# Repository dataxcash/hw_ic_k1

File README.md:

# hw_ic_k1 — K1 Master Gate Card (PCIe 2.1 x2 Injection)

*K1 Master Gate Card — final 4K top render (ECN-14/15/16 complete). USB Type-C
re-mounted facing the board's left edge; all 15 high-speed nets re-routed and
length-matched (intra-pair skew ≤ 0.10 mm); H5 mounting hole added — 47
components, 5 mounting holes. J1 body uses the Amphenol stand-in STEP; the JAE
DX07S024WJ1R350 model is pending.*

Open-source hardware — KiCad design files for the **K1 Master Gate Card**,
the master-side converter card in the IOCONVERT V2.0 1-Master-to-4-Worker
chained NTB cluster.

## Overview

K1 sits at the **master side** of a PCIe NTB chain. It provides USB Type-C
management access, pre-authentication gating (SE050 via I2C), and a PCIe
2.1 x2 data path injected into the master host through an OCuLink connector.

```
KEY (secure vault) ──Type-C──► K1 Master Gate Card ──OCuLink──► Master Host
                                  │
                                  ├─ USB management (SBU I2C ↔ SE050 pre-auth)
                                  ├─ PCIe 2.1 x2 lane injection
                                  └─ 5V pre-auth power rail (TLV61046 boost)
```

## Key Features

- **Form factor**: 80 × 38 mm, 4-layer PCB
- **Interface**: USB Type-C (KEY), OCuLink SFF-8612 (host), 12V DC-in
- **Security**: STM32G0B1 MCU gatekeeper + SE050 pre-authentication via SBU I2C
- **Data path**: PCIe 2.1 x2 with PI3DBS16412 lane-swap MUX
- **Power**: 3.3V_AUX → 5V boost (TLV61046), LDO 5V→3V3, 12V→3V3 DC-DC
- **Management**: OOB UART passthrough, opto-isolated power button (LTV-356T)

## Repository Contents

| Path | Description |
|---|---|
| `k1_v1.kicad_pro` / `.kicad_pcb` | KiCad 10 project + PCB (self-contained) |
| `sch/` | Schematics: connectors, MCU & sideband, power (12V/5V/3V3), decoupling |
| `lib/IOCONVERT.kicad_sym` | Symbol library (80 symbols) — required for schematics |
| `lib/ForgeOS.pretty/` | Footprint library (19 footprints) |
| `boards/` | Board/nets configuration (YAML) |

## Getting Started

1. Install [KiCad](https://www.kicad.org/) 10.x
2. Clone this repository
3. Open `k1_v1.kicad_pro`
4. If symbols/footprints show as missing, add `lib/IOCONVERT.kicad_sym`
   to the symbol library table and `lib/ForgeOS.pretty/` to the footprint
   library table (global or project-level)

## License

AGPL-3.0 (see `LICENSE`)

---

*Part of the IOCONVERT V2.0 family: [hw_ic_k2](https://github.com/dataxcash/hw_ic_k2) (worker data-plane card) · [hw_ic_key](https://github.com/dataxcash/hw_ic_key) (secure key vault)*

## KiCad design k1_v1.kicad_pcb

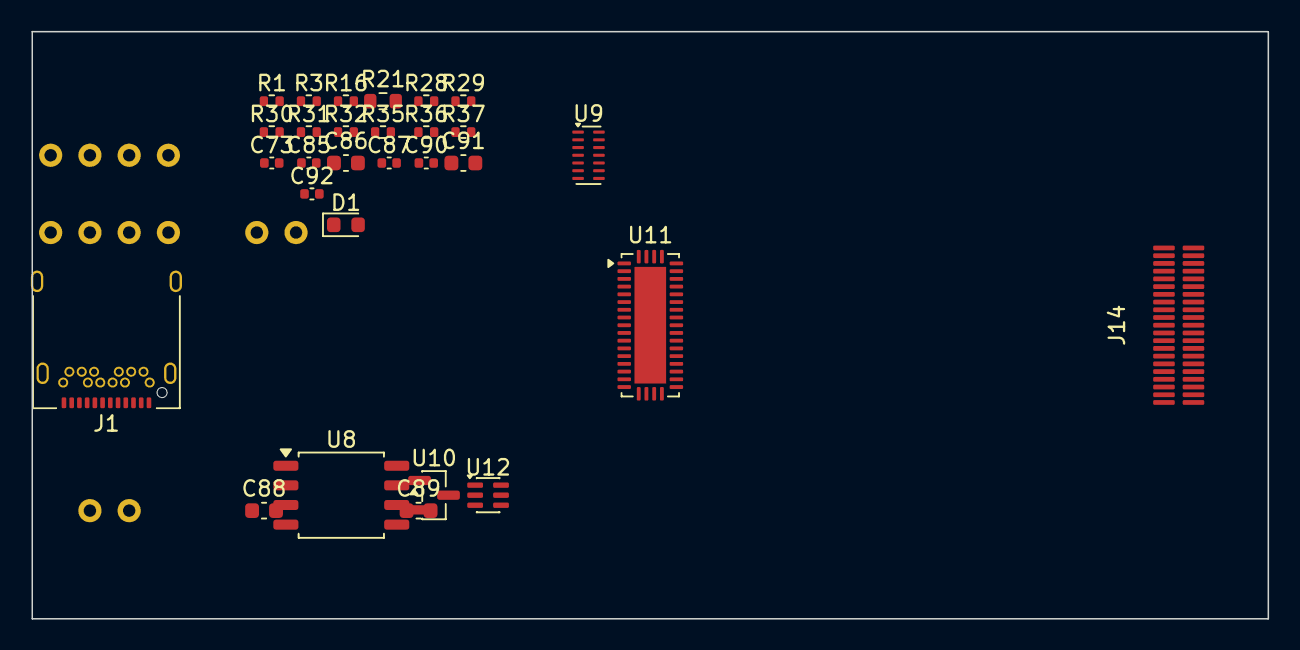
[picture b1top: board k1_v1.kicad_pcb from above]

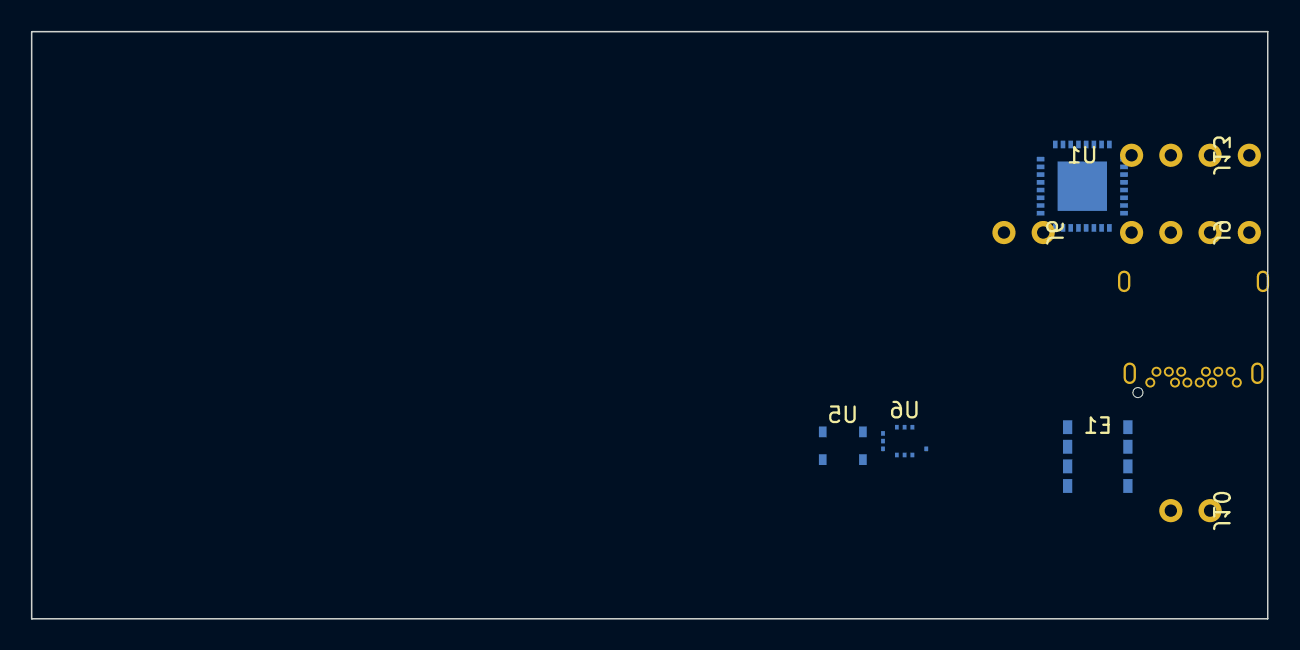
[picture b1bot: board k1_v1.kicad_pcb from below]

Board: 4 copper layers, 80.0 x 38.0 mm, 37 parts (8 on the bottom side), 47 nets, no tracks yet.

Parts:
C73, C85, C87, C90, C92: C_0402_1005Metric
C86, C88, C89, C91: C_0603_1608Metric
D1: LED_0603_1608Metric
E1: SOIC8_FRU
J1: USB_C_Receptacle_Amphenol_12401548E4-2A
J6, J10: PinHeader_1x02
J9, J13: PinHeader_1x04
J14: OCuLink_SFF8612
R1, R3, R16, R28, R29, R30, R31, R32, R35, R36, R37: R_0402_1005Metric
R21: R_0603_1608Metric
U1: MCU_STM32G0_QFN32
U5: OPTO_LTV356T
U6: TS3USB221A_UQFN10
U8: SOIC-8_5.3x5.3mm_P1.27mm
U9: TPD6E05U06_RVZ
U10: SOT-23
U11: PI3DBS16412
U12: TPS22919

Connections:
12V_IN: C88.1, J10.1, U8.4, U8.6
CC1: J1.A5, R35.2
CC2: J1.B5, R36.2
GND: C73.2, C85.2, C86.2, C87.2, C88.2, C89.2, C90.2, C91.2, C92.2, D1.2, E1.1, E1.4, J1.A1, J1.A12, J1.B1, J1.B12, J6.2, J10.2, J14.A2, J14.A5, J14.A8, J14.A11, J14.A13, J14.A14, J14.A17, J14.A20, J14.B2, J14.B5, J14.B8, J14.B11, J14.B14, J14.B17, J14.B20, R16.2, R28.2, R37.2, U1.8, U1.22, U1.32, U5.4, U6.1, U8.2, U9.13, U9.14, U11.4, U11.14, U11.19, U11.21, U11.39, U11.41, U11.CP, U12.2
GPIO_LED: R21.1, U1.24
I2C1_SCL: E1.5, R31.1, U1.11, U6.2
I2C1_SDA: E1.6, R32.1, U1.12, U6.3
KEY_D_N: J1.A7, U9.2
KEY_D_P: J1.A6, U9.1
LED_A: D1.1, R21.2
MCU_VDD: C85.1, C86.1, E1.8, R29.2, R30.2, R31.2, R32.2, U1.21
MUX_PD: U1.14, U11.1, U11.10
MUX_SEL: U1.15, U11.8, U11.17
NC: U11.18, U11.42
NRST: C73.1, R29.1, U1.1
OCuLink_RX0_N: J14.B4, U11.31
OCuLink_RX0_P: J14.B3, U11.32
OCuLink_RX1_N: J14.B7, U11.22
OCuLink_RX1_P: J14.B6, U11.23
OCuLink_TX0_N: J14.A4, U11.33
OCuLink_TX0_P: J14.A3, U11.34
OCuLink_TX1_N: J14.A7, U11.24
OCuLink_TX1_P: J14.A6, U11.25
P3V3_AUX: C90.1, C91.1, R1.2, R30.1, U1.7, U6.10, U11.5, U11.9, U11.13, U11.20, U11.30, U11.40
PCIE_RX0_N: J1.B10, U9.6, U11.7
PCIE_RX0_P: J1.B11, U9.5, U11.6
PCIE_RX1_N: J1.A10, U11.16
PCIE_RX1_P: J1.A11, U11.15
PCIE_TX0_N: J1.A2, U9.4, U11.3
PCIE_TX0_P: J1.A3, U9.3, U11.2
PCIE_TX1_N: J1.B2, U11.12
PCIE_TX1_P: J1.B3, U11.11
PERSTA#: C87.1, R1.1, U1.4
PWR_5V_KEY: C89.1, U8.5, U12.1
PWR_5V_PREAUTH: C92.1, J1.A4, J1.A9, J1.B4, J1.B9, R35.1, R36.1, U12.6
PWR_BTN_ISO: R3.2, U5.1, U5.2
PWR_BTN_OUT: R3.1, U1.23
PWR_CTRL_OUT: J6.1, U5.3
SBU1: J1.A8, R37.1, U1.17, U6.4
SBU2: J1.B8, U6.5
SBU_EN: U1.31, U6.9
SBU_SEL: R16.1, U1.6, U6.8
SWCLK_BOOT0: J13.1, R28.1, U1.20
SWDIO: J13.2, U1.19
TPS_EN: U1.26, U12.3
UART_RX: J9.2, U1.18
UART_TX: J9.1, U1.13

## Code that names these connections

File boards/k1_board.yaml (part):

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    - I2C1_SDA
    - PERSTA#
    - PWR_BTN_OUT
    - GPIO_LED
    - UART_TX
    - UART_RX
    - P3V3_AUX
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    footprint: ForgeOS:PinHeader_1x04
    sch_pins: 4
    fp_pads: 4
    function: SWD 4-pin 调试口 (工厂烧录 + SWCLK_BOOT0)
    geometry:
      bbox:
      - 1.5
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      source: footprint
      provenance: AppDir/usr/share/kicad/footprints/Resistor_SMD.pretty/R_0603_1608Metric.kicad_mod
    nets:
    - GPIO_LED
    - LED_A
  R28:
    value: 10K
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  - J6
- function: 状态 LED
  nets:
  - GPIO_LED
  - LED_A
  devices:
  - U1
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  - U5/COLLECTOR
  - J6/PWR_BTN#
  candidate_routable: true
- net: GPIO_LED
  domain: control
  members:
  - U1/GPIO_LED
  - R21/A
  candidate_routable: true
- net: LED_A
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    netlist_unconnected: 40
    note: '差 4: U6/D_P_B, U6/D_N_B, U8/FB, U8/SW 未列入 k1_nets nc list'
  k1_nets_yaml_missing_nodes:
  - 'SBU_SEL: U1/PB8 (pad31) — yaml 仅 R16/U6'
  - 'SBU_EN: U1/PB9 (pad1) — yaml 仅 U6/OE#'
  - 'MUX_PD: U1/PA7 (pad14) — yaml 仅 U11/PD1,PD2'
  - 'TPS_EN: U1/PB3 (pad26) — yaml 仅 U12/ON'
  - 'SBU1: U1/PB2 (pad17) — yaml 缺'
  - 'PWR_5V_PREAUTH: C92/A — yaml 缺 (C92 全器件)'
  - 'GND: C92/B — yaml 缺'
  open_issues:
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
